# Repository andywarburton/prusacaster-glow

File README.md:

# prusacaster-glow
Build your own 3d printed WLED powered sound reactive  electric guitar

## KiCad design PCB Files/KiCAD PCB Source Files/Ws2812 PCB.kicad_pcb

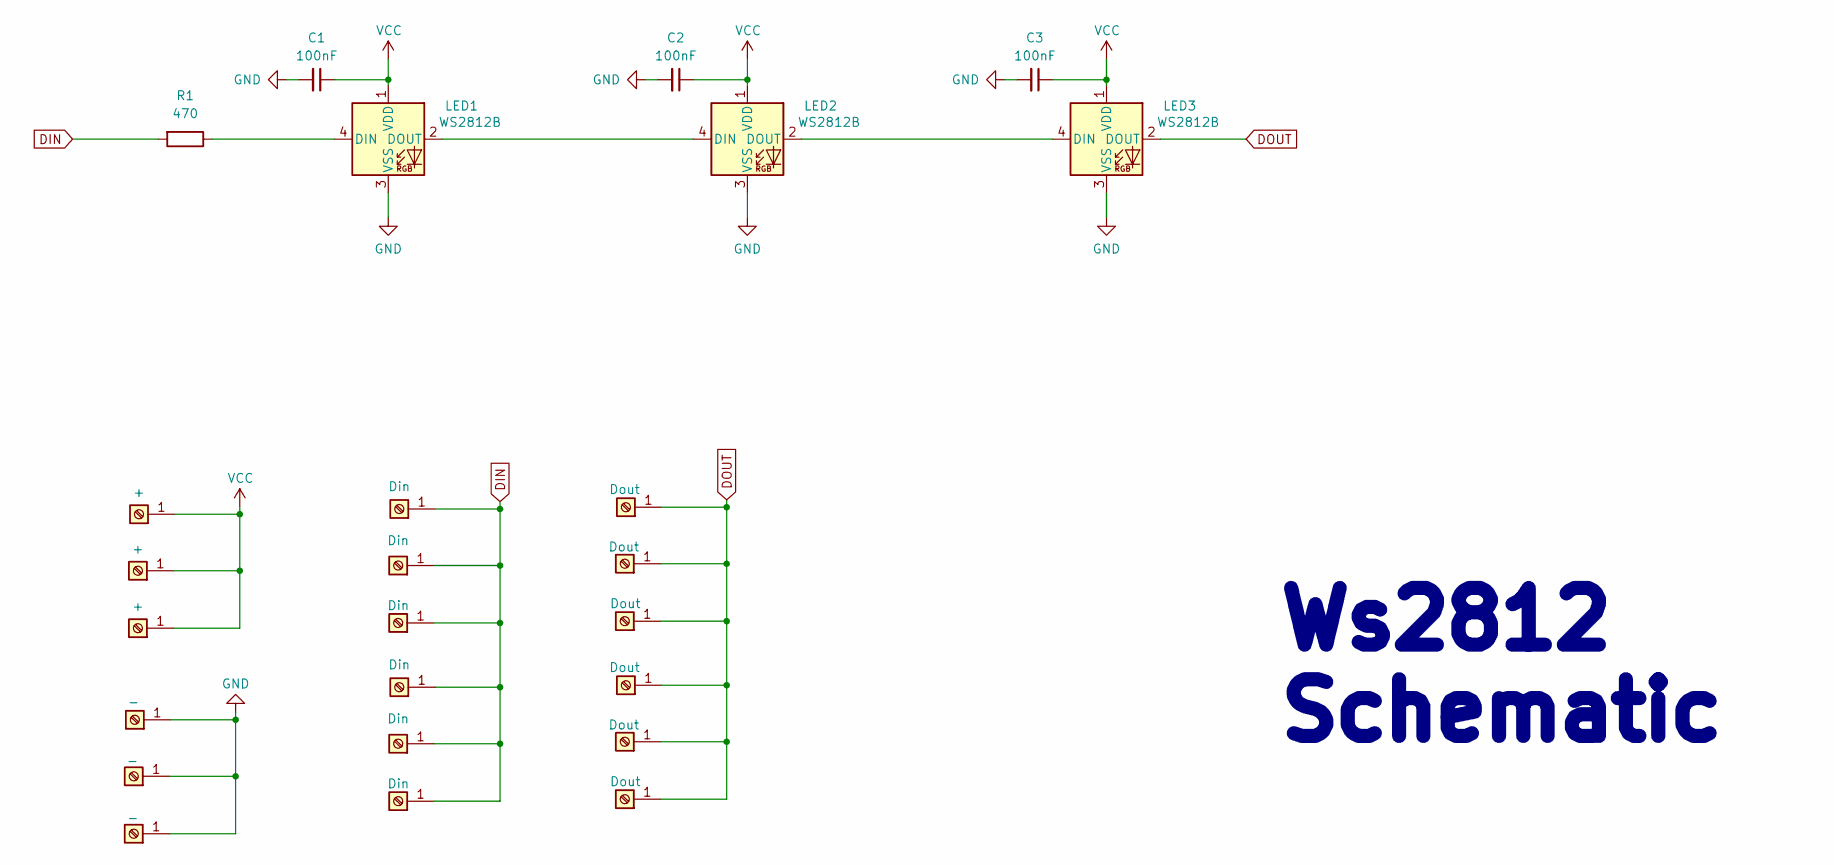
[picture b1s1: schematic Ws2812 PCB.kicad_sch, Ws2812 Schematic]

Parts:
C1, C2, C3: 100nF; C_0603_1608Metric; JLCPCB Part# C14663
J1, J2, J3: -; 1X01_CASTEL
J4, J5, J6: +; 1X01_CASTEL
J7, J8, J9, J16, J17, J18: Dout; 1X01_CASTEL
J10, J11, J12, J13, J14, J15: Din; 1X01_CASTEL
LED1, LED2, LED3: WS2812B; LED_WS2812B_PLCC4_5.0x5.0mm_P3.2mm; JLCPCB Part# C2761795
R1: 470; R_0603_1608Metric; JLCPCB Part# C23179

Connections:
DIN: J10.1, J11.1, J12.1, J13.1, J14.1, J15.1, R1.2
DOUT: J7.1, J8.1, J9.1, J16.1, J17.1, J18.1, LED3.2 (DOUT)
GND: C1.2, C2.2, C3.2, J1.1, J2.1, J3.1, LED1.3 (VSS), LED2.3 (VSS), LED3.3 (VSS)
unnamed: LED1.4 (DIN), R1.1
unnamed: LED1.2 (DOUT), LED2.4 (DIN)
unnamed: LED2.2 (DOUT), LED3.4 (DIN)
VCC: C1.1, C2.1, C3.1, J4.1, J5.1, J6.1, LED1.1 (VDD), LED2.1 (VDD), LED3.1 (VDD)

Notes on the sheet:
Ws2812 Schematic

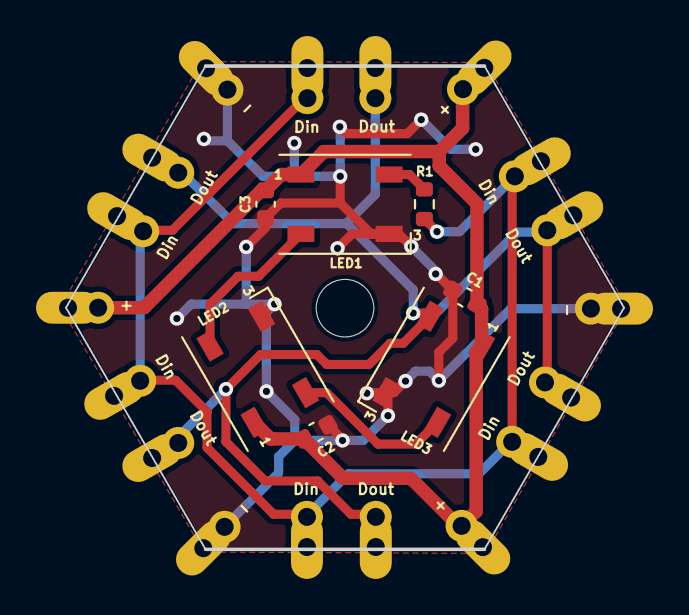
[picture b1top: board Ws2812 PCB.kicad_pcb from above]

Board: 2 copper layers, 31.0 x 26.8 mm, 25 parts (0 on the bottom side), 7 nets.

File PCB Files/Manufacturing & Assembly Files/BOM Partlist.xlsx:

Item | Qty | Reference(s) | Value | Footprint | JLCPCB Part# | Purchase Link | Alternative Part#
1 | 3 | C1, C2, C3 | 100nF | Ahsan Libs:C_0603_1608Metric | C14663 | https://www.lcsc.com/product-detail/Multilayer-Ceramic-Capac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
2 | 3 | LED1, LED2, LED3 | WS2812B | Ahsan Libs:LED_WS2812B_PLCC4_5.0x5.0mm_P3.2mm | C2761795 | https://www.lcsc.com/product-detail/Light-Emitting-Diodes-LE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 | https://www.lcsc.com/product-detail/Light-Emitting-Diodes-LE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
3 | 1 | R1 | 470 | Ahsan Libs:R_0603_1608Metric | C23179 | https://www.lcsc.com/product-detail/Chip-Resistor-Surface-Mo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

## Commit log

2024-03-23 Added PCB files
